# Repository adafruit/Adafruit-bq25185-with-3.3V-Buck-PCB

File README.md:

## Adafruit bq25185 USB / DC / Solar Charger with 3.3V Buck Board PCB

<a href="http://www.adafruit.com/products/6092"><br/>
Click here to purchase one from the Adafruit shop</a>

PCB files for the Adafruit bq25185 USB / DC / Solar Charger with 3.3V Buck Board. 

Format is EagleCAD schematic and board layout
* https://www.adafruit.com/product/6092

### Description

We're always on the look out for better ways to make projects portable: being able to charge your battery in the most convenient manner will let projects run no matter what power is available. Then we added a power supply chip with it to let you run your project without a separate board. The result is the Adafruit bq25185 USB / DC / Solar Charger with 3.3V Buck Board!

It uses the new bq25185 is a nifty charger chip with fairly high charge current, power path support, and the ability to charge from USB, DC or solar power. It's also a great value, so it's a good upgrade from MCP73833 or MCP73831-based charger boards. The buck converter is the TPS62569, which will give a clean 1 Amp output with good efficiency, to squeeze the most power possible out of your battery.

This board is meant to be everything you need to power your 3.3V electronics: simply connect a 500mAh or larger battery to the JST PH 2-pin port, then charge it when you can from USB or DC/solar. At the other end is a terminal block which will provide the power-path-load output from the bq25185 which will range from 3.0V (battery near-dead) to 4.5V (USB/DC/Solar is powering the board) at about 1 Amp max. Another terminal port will give 3.3V output, up to 1 A (this will also dip down to 3.0V when the battery is near-empty)

* USB Type C connector with 5.1k CC resistors so it will work with any computer or power supply to get 5V and up to 1A. Data lines available if needed, on the bottom breakout.
* Separate DC or Solar Input - Two pads on the edge can be used to connect a 5 ~ 18V power supply, which can be used instead of USB. If the input is a solar panel, the charging chip will adjust the current draw so that the voltage does not dip below the battery, thus optimizing the solar power input. No large capacitor needed to stabilize it, and you get near-MPPT capability without the cost and complexity of MPPT.
* Default charge rate of 1A, but you can cut the jumper on the back to set the rate to 500mA
* Power Path to Load - If the 4.5V or 3.3V load connector is drawing current while the USB / DC/Solar power is attached, it will default to drawing current from the charger and any left over current will go to the battery. That keeps your battery from constantly charging/discharging which will reduce the battery life.
* Regulated 4.5V-max Output - no matter what voltage you have on the USB or DC / solar inputs, the 4.5V terminal block output port will never go above 4.5V due to an internal voltage regulator. Keep this in mind, though, when dealing with high currents and high DC voltages as the LDO will make the board start to overheat and throttle the current.
* Regulated 3.3V-max Output - a seperate buck converter will take the load output from the bq25185 and switch it down to 3.3V at 1 Amp max load
* Three Status LEDs - Orange Charging LED, red Fault LED, and Green 3.3V output LED.
* Enable pad - to disable the 3.3V buck converter.
* Mounting holes!

This board is pretty much plug-and-play. Change the charging jumper if you like, then connect your battery to the BATT port, and the 4.5V-max and 3.3V-max outputs go to your circuit. Don't forget the two outputs  will never go above 4.5V or 3.3V, but it can go as low as 3.0V if the battery is nearly empty. You can monitor the voltage on the battery via the secondary pads on the bottom edge, if necessary.

To use with solar, pick up a 5~7V solar panel (using a higher voltage panel will only lose the extra voltage as heat so there's no benefit to going over 7V), and either cut the connector off to wire it directly, or use a 2.1mm adapter cable plus a 2.1mm terminal block to get two wires for the DC Input port.

If you need a board with higher charge current or a DC plug already on-board, check out the bq24074 which has up to 1.5A charge rate and a on-board 2.1mm DC jack. It doesn't have a buck converter but you could wire up the TPS62569 separately

### License

Adafruit invests time and resources providing this open source design, please support Adafruit and open-source hardware by purchasing products from [Adafruit](https://www.adafruit.com)!

Designed by Limor Fried/Ladyada for Adafruit Industries.

Creative Commons Attribution/Share-Alike, all text above must be included in any redistribution. 
See license.txt for additional details.

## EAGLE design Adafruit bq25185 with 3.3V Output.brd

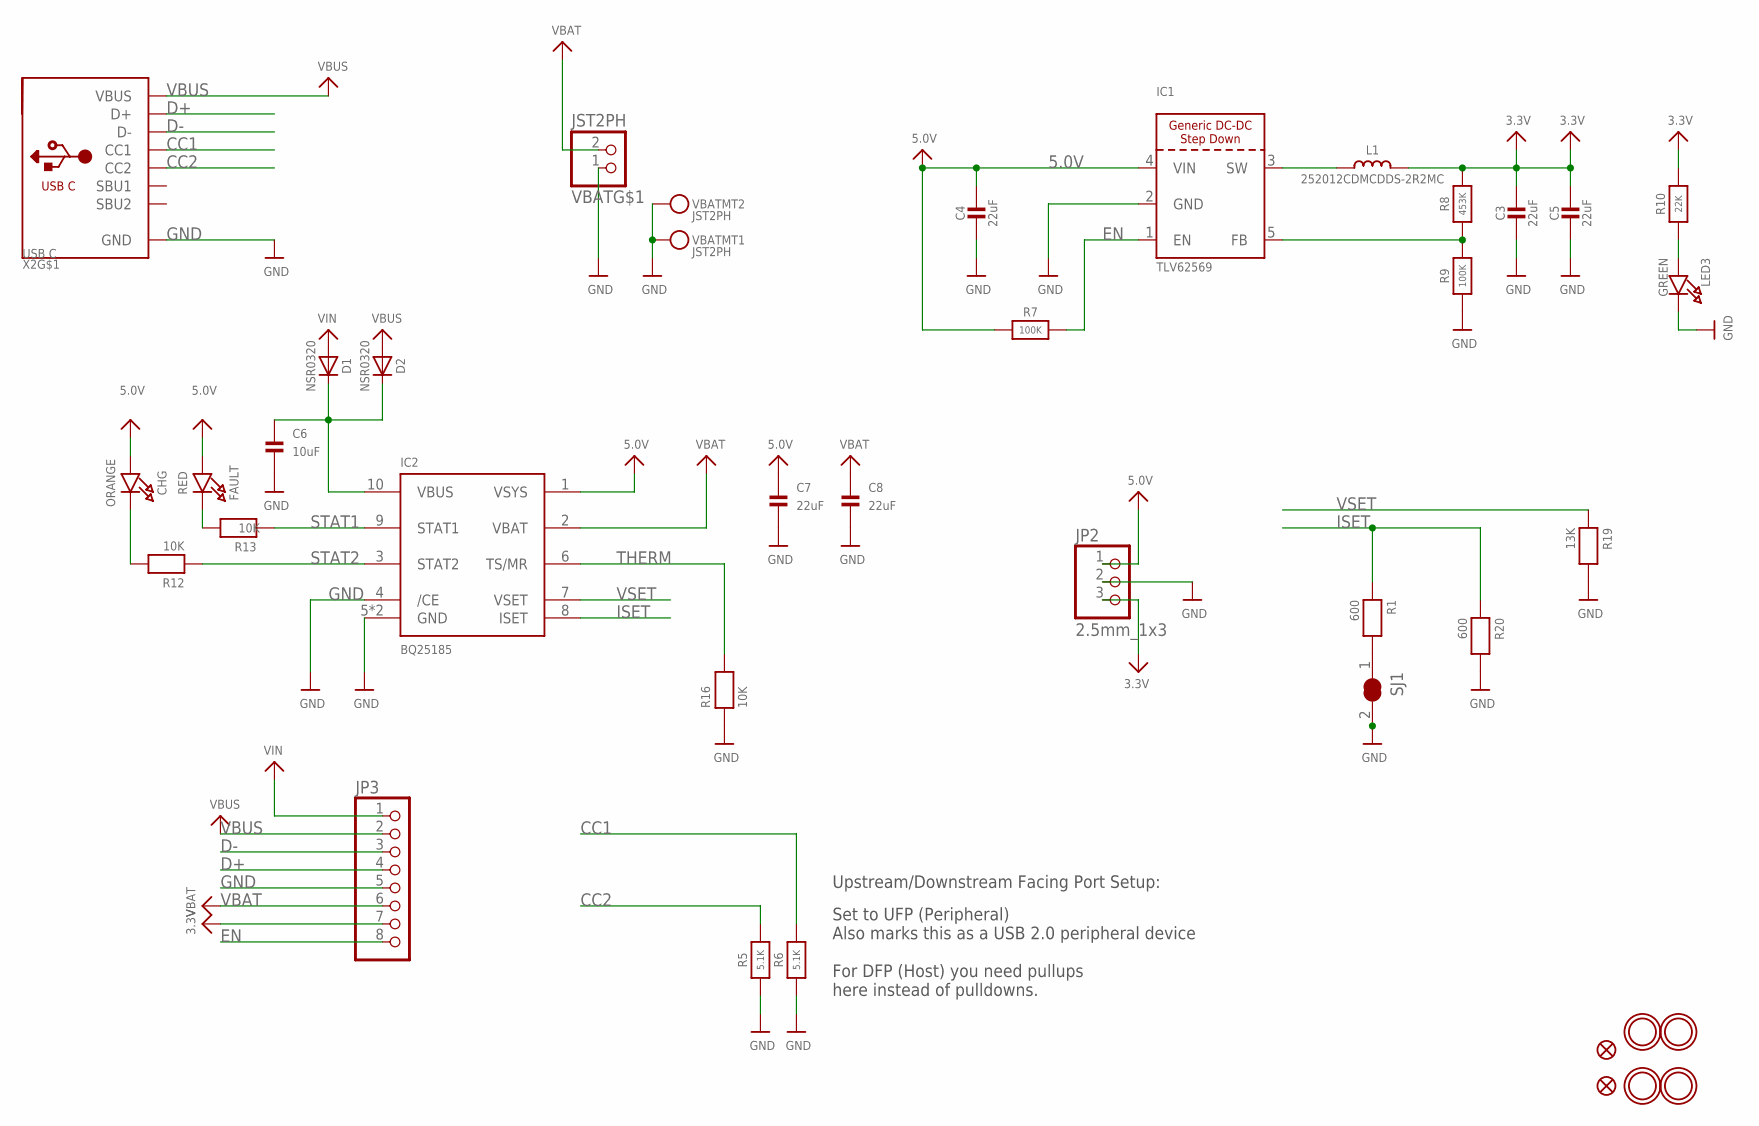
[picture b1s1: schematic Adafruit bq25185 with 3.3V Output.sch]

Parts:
C3, C4, C5, C7, C8: 22uF; 0805-NO
C6: 10uF; 0805-NO
CHG: ORANGE; CHIPLED_0603_NOOUTLINE
D1, D2: NSR0320; SOD-323_MINI
FAULT: RED; CHIPLED_0603_NOOUTLINE
FID1, FID2: FIDUCIAL_0.5MM
IC1: TLV62569; SOT23-5
IC2: BQ25185; WSON10
JP2: 2.5mm_1x3; 1X03_2.54MMTERMINAL
JP3: HEADER-1X870MIL; 1X08_ROUND_70
L1: 252012CDMCDDS-2R2MC; INDUCTOR_TAIYOYUDEN_NRH2412T
LED3: GREEN; CHIPLED_0603_NOOUTLINE
R1, R20: 600; _0402NO
R5, R6: 5.1K; _0402NO
R7, R9: 100K; _0402NO
R8: 453K; _0402NO
R10: 22K; _0402NO
R12, R13, R16: 10K; _0402NO
R19: 13K; _0402NO
SJ1: SOLDERJUMPER_CLOSED; SOLDERJUMPER_CLOSEDWIRE
U$9, U$10, U$11, U$12: MOUNTINGHOLE2.5; MOUNTINGHOLE_2.5_PLATED
VBAT: JST2PH; JSTPH2_BATT
X2: USB C; USB_C_CUSB31-CFM2AX-01-X

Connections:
3.3V: C3.1, C5.1, JP2.3, JP3.7, L1.2, R8.2, R10.2
5.0V: C4.1, C7.1, CHG.A, FAULT.A, IC1.4 (VIN), IC2.1 (VSYS), JP2.1, R7.1
CC1: R6.2, X2.A5 (CC1)
CC2: R5.2, X2.B5 (CC2)
D+: JP3.4, X2.A6 (D+), X2.B6 (D+)
D-: JP3.3, X2.A7 (D-), X2.B7 (D-)
EN: IC1.1 (EN), JP3.8, R7.2
FB: IC1.5 (FB), R8.1, R9.2
GND: C3.2, C4.2, C5.2, C6.2, C7.2, C8.2, IC1.2 (GND), IC2.4 (/CE), IC2.5 (GND), IC2.PAD (GND), JP2.2, JP3.5, LED3.C, R5.1, R6.1, R9.1, R16.1, R19.2, R20.2, SJ1.2, VBAT.1, VBAT.NC1, VBAT.NC2, X2.A1B12 (GND), X2.B1A12 (GND)
ISET: IC2.8 (ISET), R1.1, R20.1
unnamed: R1.2, SJ1.1
unnamed: C6.1, D1.C, D2.C, IC2.10 (VBUS)
unnamed: IC1.3 (SW), L1.1
unnamed: CHG.C, R12.2
unnamed: LED3.A, R10.1
unnamed: FAULT.C, R13.2
STAT1: IC2.9 (STAT1), R13.1
STAT2: IC2.3 (STAT2), R12.1
THERM: IC2.6 (TS/MR), R16.2
VBAT: C8.1, IC2.2 (VBAT), JP3.6, VBAT.2
VBUS: D2.A, JP3.2, X2.A4B9 (VBUS), X2.B4A9 (VBUS)
VIN: D1.A, JP3.1
VSET: IC2.7 (VSET), R19.1

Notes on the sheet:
Set to UFP (Peripheral) Also marks this as a USB 2.0 peripheral device For DFP (Host) you need pullups here instead of pulldowns.
Upstream/Downstream Facing Port Setup:

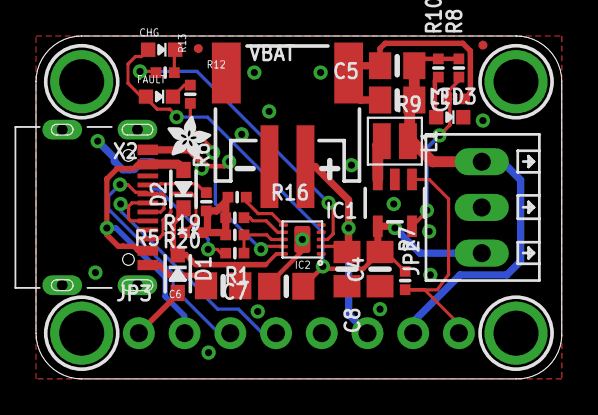
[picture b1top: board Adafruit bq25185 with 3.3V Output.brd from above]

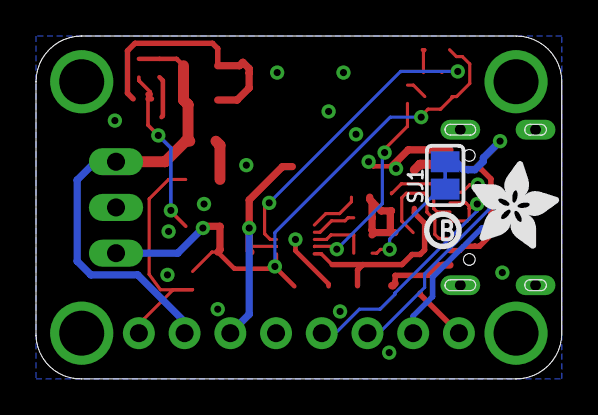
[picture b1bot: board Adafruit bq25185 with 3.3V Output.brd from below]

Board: 2 copper layers, 29.2 x 19.1 mm, 61 parts (11 on the bottom side), 23 nets.

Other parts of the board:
PLABEL0: PLABEL0
PLABEL1: PLABEL1
PLABEL2: PLABEL2
PLABEL3: PLABEL3
PLABEL4: PLABEL4
PLABEL5: PLABEL5
PLABEL6: PLABEL6
PLABEL7: PLABEL7
PLABEL8: PLABEL8
PLABEL9: PLABEL9
PLABEL10: PLABEL10
PLABEL11: PLABEL11
PLABEL12: PLABEL12
PLABEL13: PLABEL13
PLABEL14: PLABEL14
PLABEL15: PLABEL15
PLABEL16: PLABEL16
PLABEL17: PLABEL17
PLABEL18: PLABEL18
PLABEL19: PLABEL19
PLABEL20: PLABEL20
U$2: PCBFEAT-REV-040
U$26: ADAFRUIT_5MM
U$34: ADAFRUIT_2.5MM

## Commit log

2024-11-22 cookiecutter

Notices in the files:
parts and their libraries:
microbuilder: This work is placed in the public domain, and may be freely used for commercial and non-commercial work with the following conditions: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
